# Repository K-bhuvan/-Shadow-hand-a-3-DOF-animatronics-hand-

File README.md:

# -Shadow-hand-a-3-DOF-animatronics-hand-
 Goal is to classify human behavior using support vector machines. Performed on Microsoft daily activity dataset.
Video Demonstration: https://youtu.be/kKWgIvSmsIc

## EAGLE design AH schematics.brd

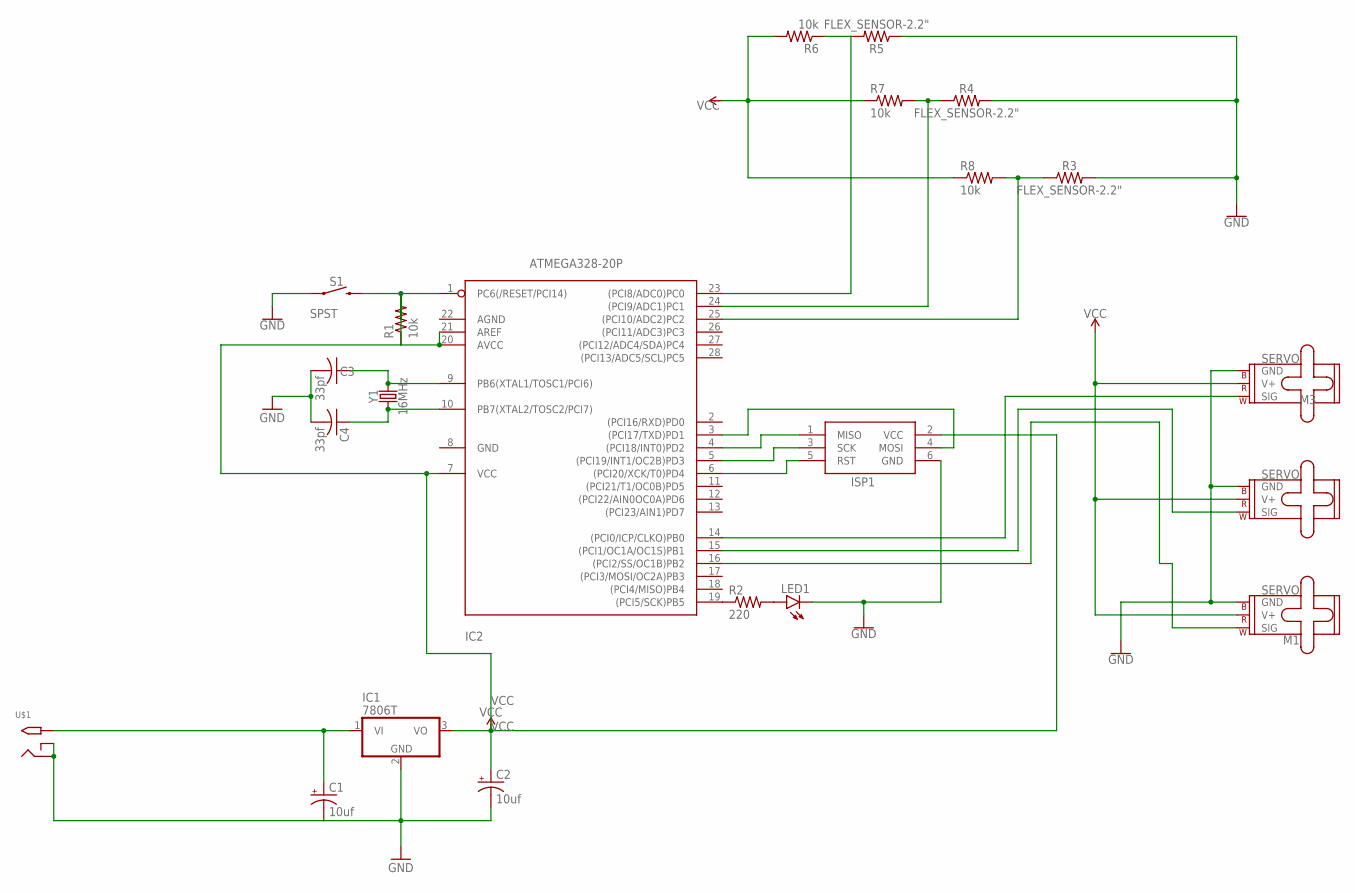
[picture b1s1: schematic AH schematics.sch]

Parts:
C1, C2: 10uf; E3,5-8
C3, C4: 33pf; C025-024X044
IC1: 7806T; TO220H
IC2: ATMEGA328-20P; DIL28-3
ISP1: AVRISP-6; AVRISP
LED1: LED3MM
M1, M2, M3: SERVO; 1X03
R1, R6, R7, R8: 10k; 0204/7
R2: 220; 0204/7
R3, R4, R5: FLEX_SENSOR-2.2"; FLEX_SENSOR
S1: SPST; TACTILE_SWITCH_PTH_6.0MM
U$1: 2.1MMJACKSMT; DCJACK_2MM_SMT
Y1: 16MHz; HC49US

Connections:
GND: C1.-, C2.-, C3.2, C4.2, IC1.2 (GND), ISP1.6 (GND), LED1.A, LED1.K (C), M1.3 (GND), M2.3 (GND), M3.3 (GND), R2.2, R3.P$2 (2), R4.P$2 (2), R5.P$1 (1), S1.1, U$1.GND (RING), U$1.GNDBREAK (RING_SW)
unnamed: C1.+, IC1.1 (VI), U$1.PWR2 (TIP)
unnamed: IC2.19 ((PCI5/SCK)PB5), R2.1
unnamed: IC2.1 (PC6(/RESET/PCI14)), R1.1, R1.2, S1.3 (2)
unnamed: C3.1, IC2.9 (PB6(XTAL1/TOSC1/PCI6)), Y1.2
unnamed: C4.1, IC2.10 (PB7(XTAL2/TOSC2/PCI7)), Y1.1
unnamed: IC2.16 ((PCI2/SS/OC1B)PB2), M1.1 (SIG)
unnamed: IC2.14 ((PCI0/ICP/CLKO)PB0), M3.1 (SIG)
unnamed: IC2.5 ((PCI19/INT1/OC2B)PD3), ISP1.3 (SCK)
unnamed: IC2.6 ((PCI20/XCK/T0)PD4), ISP1.5 (RST)
unnamed: IC2.4 ((PCI18/INT0)PD2), ISP1.1 (MISO)
unnamed: IC2.3 ((PCI17/TXD)PD1), ISP1.4 (MOSI)
unnamed: IC2.24 ((PCI9/ADC1)PC1), R4.P$1 (1), R7.2
unnamed: IC2.23 ((PCI8/ADC0)PC0), R5.P$2 (2), R6.1
unnamed: IC2.25 ((PCI10/ADC2)PC2), R3.P$1 (1), R8.2
unnamed: IC2.15 ((PCI1/OC1A/OC1S)PB1), M2.1 (SIG)
VCC: C2.+, IC1.3 (VO), IC2.7 (VCC), IC2.20 (AVCC), IC2.21 (AREF), ISP1.2 (VCC), M1.2 (V+), M2.2 (V+), M3.2 (V+), R6.2, R7.1, R8.1

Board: 2 copper layers, 22 parts (0 on the bottom side), 17 nets, no tracks yet.

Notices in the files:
parts and their libraries:
SparkFun-Electromechanical: Licensing: Creative Commons ShareAlike 4.0 International - https://creativecommons.org/licenses/by-sa/4.0
